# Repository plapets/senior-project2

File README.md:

# senior-project2

This repository contains my contributions to a two-person senior project.

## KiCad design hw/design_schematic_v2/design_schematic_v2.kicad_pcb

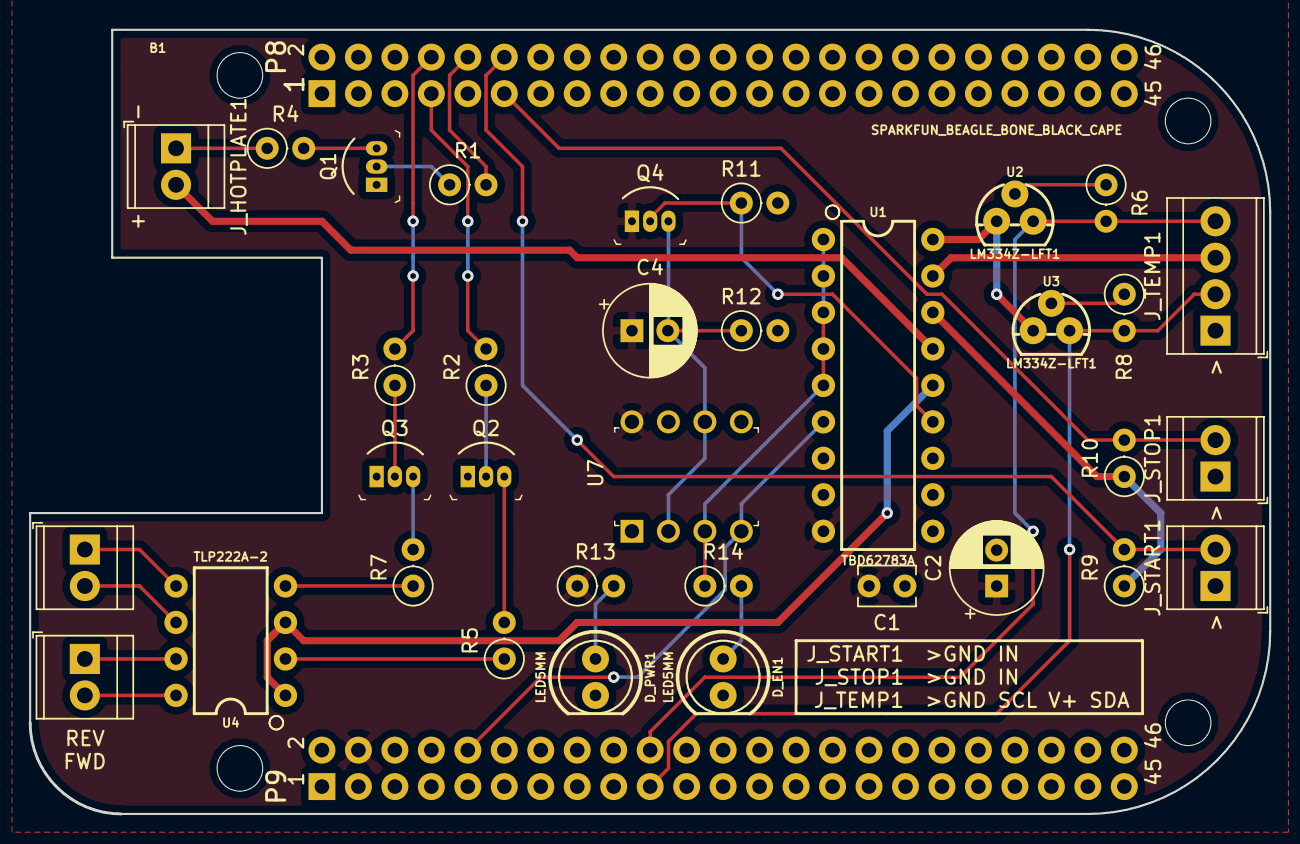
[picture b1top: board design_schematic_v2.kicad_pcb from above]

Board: 2 copper layers, 86.3 x 54.6 mm, 35 parts (0 on the bottom side), 35 nets.

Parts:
B1: SPARKFUN_BEAGLE_BONE_BLACK_CAPE; BEAGLE_BONE_BLACK_CAPE
C1: 0.1u; C_Disc_D3.8mm_W2.6mm_P2.50mm
C2, C4: 100u; CP_Radial_D6.3mm_P2.50mm
D_EN1: LED5MM; LED_5MM
D_PWR1: LED5MM; LED_5MM
J_CONVEYOR_FWD1: Screw_Terminal_01x02; TerminalBlock_TE_282834-2_1x02_P2.54mm_Horizontal
J_CONVEYOR_REV1: Screw_Terminal_01x02; TerminalBlock_TE_282834-2_1x02_P2.54mm_Horizontal
J_HOTPLATE1: Screw_Terminal_01x02; TerminalBlock_TE_282834-2_1x02_P2.54mm_Horizontal
J_START1: Screw_Terminal_01x02; TerminalBlock_TE_282834-2_1x02_P2.54mm_Horizontal
J_STOP1: Screw_Terminal_01x02; TerminalBlock_TE_282834-2_1x02_P2.54mm_Horizontal
J_TEMP1: Screw_Terminal_01x04; TerminalBlock_TE_282834-4_1x04_P2.54mm_Horizontal
Q1, Q2, Q3: 2N3904BU; TO-92-3
Q4: 2N3906BU; TO-92-3
R1, R2, R3, R9, R10: 24K; R_Axial_DIN0207_L6.3mm_D2.5mm_P2.54mm_Vertical
R4: 0R; R_Axial_DIN0207_L6.3mm_D2.5mm_P2.54mm_Vertical
R5, R7, R13, R14: 180; R_Axial_DIN0207_L6.3mm_D2.5mm_P2.54mm_Vertical
R6, R8: 220R; R_Axial_DIN0207_L6.3mm_D2.5mm_P2.54mm_Vertical
R11: 750; R_Axial_DIN0207_L6.3mm_D2.5mm_P2.54mm_Vertical
R12: 100K; R_Axial_DIN0207_L6.3mm_D2.5mm_P2.54mm_Vertical
U1: TBD62783A; DIP18
U2, U3: LM334Z-LFT1; TO-92
U4: TLP222A-2; DIP08
U7: TLC555CP; DIP-8_W7.62mm

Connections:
+3V3: B1.P9.4, C1.2, C2.1, C4.1, Q4.1, R13.1, U1.9, U7.8
/GPIO_CONVEYOR_FWD: B1.P8.7, R2.2
/GPIO_CONVEYOR_REV: B1.P8.8, R3.2
/GPIO_HOTPLATE: B1.P8.10, R1.2
/GPIO_START: B1.P8.11, J_STOP1.2, R10.2
/GPIO_STOP: B1.P8.12, J_START1.2, R9.2
/SCL_TEMP: B1.P9.19, J_TEMP1.2, R8.2, U3.3
/SDA_TEMP: B1.P9.20, J_TEMP1.4, R6.2, U2.3
/SYS_ENABLE: R14.1, U1.1, U1.2, U1.3, U1.4, U1.5, U7.3
/VCC_EN_CONVEYOR: U1.14, U4.1, U4.3
/VCC_EN_HOTPLATE: J_HOTPLATE1.2, U1.15
/VCC_PU_BUTTON: R9.1, R10.1, U1.16
/VCC_PU_SMBUS: U1.18, U2.1, U3.1
/VCC_TEMP: J_TEMP1.3, U1.17
/~SYS_RESET: B1.P9.10, U1.6, U7.4
GND: B1.P9.2, C1.1, C2.2, D_EN1.K, D_PWR1.K, J_START1.1, J_STOP1.1, J_TEMP1.1, Q1.1, Q2.1, Q3.1, R11.2, R12.2, U1.7, U1.8, U1.10, U7.1
unnamed: C4.2, Q4.3, R12.1, U7.2, U7.6
unnamed: D_EN1.A, R14.2
unnamed: D_PWR1.A, R13.2
unnamed: J_CONVEYOR_FWD1.1, U4.7
unnamed: J_CONVEYOR_FWD1.2, U4.8
unnamed: J_CONVEYOR_REV1.1, U4.5
unnamed: J_CONVEYOR_REV1.2, U4.6
unnamed: J_HOTPLATE1.1, R4.1
unnamed: Q1.2, R1.1
unnamed: Q1.3, R4.2
unnamed: Q2.2, R2.1
unnamed: Q2.3, R5.2
unnamed: Q3.2, R3.1
unnamed: Q3.3, R7.2
unnamed: Q4.2, R11.1, U1.13
unnamed: R5.1, U4.2
unnamed: R6.1, U2.2
unnamed: R7.1, U4.4
unnamed: R8.1, U3.2

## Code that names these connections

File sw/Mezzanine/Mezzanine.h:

#ifndef MEZZANINE_H
#define MEZZANINE_H

/*
File:   Mezzanine.h
Date:   2019-04-30
Author: Peter Lapets

Description:
This file contains the API for controlling the mezzanine hardware.
*/

#include "../DEBUG_PRINT.h"

#include "gpio.h"
#include "i2c.h"

#define LOG_STREAM stderr


#define GPIO_HOTPLATE       (68)
#define GPIO_CONVEYOR_FWD   (66)
#define GPIO_CONVEYOR_REV   (67)
#define GPIO_START          (44)
#define GPIO_STOP           (45)

#define I2C_BUS                 2
#define I2C_SLAVE_ADDRESS       0x5a
#define I2C_REGISTER_T_AMBIENT  0x06
#define I2C_REGISTER_T_OBJECT   0x07
#define TEMPERATURE_ERROR_FLAG  0x8000
#define E_BAD_TEMPERATURE       -1


#define HOTPLATE_OFF        GPIO_LOW
#define HOTPLATE_ON         GPIO_HIGH

#define CONVEYOR_STOPPED    0
#define CONVEYOR_FORWARD    1
#define CONVEYOR_REVERSE    2

#define STOP_PRESSED        GPIO_HIGH
#define START_PRESSED       GPIO_LOW

int Mezzanine_HotplateInit( void );
int Mezzanine_ConveyorInit( void );
int Mezzanine_ButtonsInit( void );
int Mezzanine_TempSensorInit( void );

int Mezzanine_HotplateGetState( int * state );
int Mezzanine_HotplateSetState( int state );
int Mezzanine_ConveyorGetState( int * state );
int Mezzanine_ConveyorSetState( int state );
int Mezzanine_StopButtonGetState( int * state );
int Mezzanine_StartButtonGetState( int * state );
int Mezzanine_TempSensorGetTObject( double * celsius );

#endif /* MEZZANINE_H */

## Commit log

2019-09-11 rendered some documents as pdf
2019-09-11 added readme
2019-09-13 changed readme
